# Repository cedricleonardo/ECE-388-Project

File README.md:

# ECE-388-Project

DC Programmable Load project for ECE 388

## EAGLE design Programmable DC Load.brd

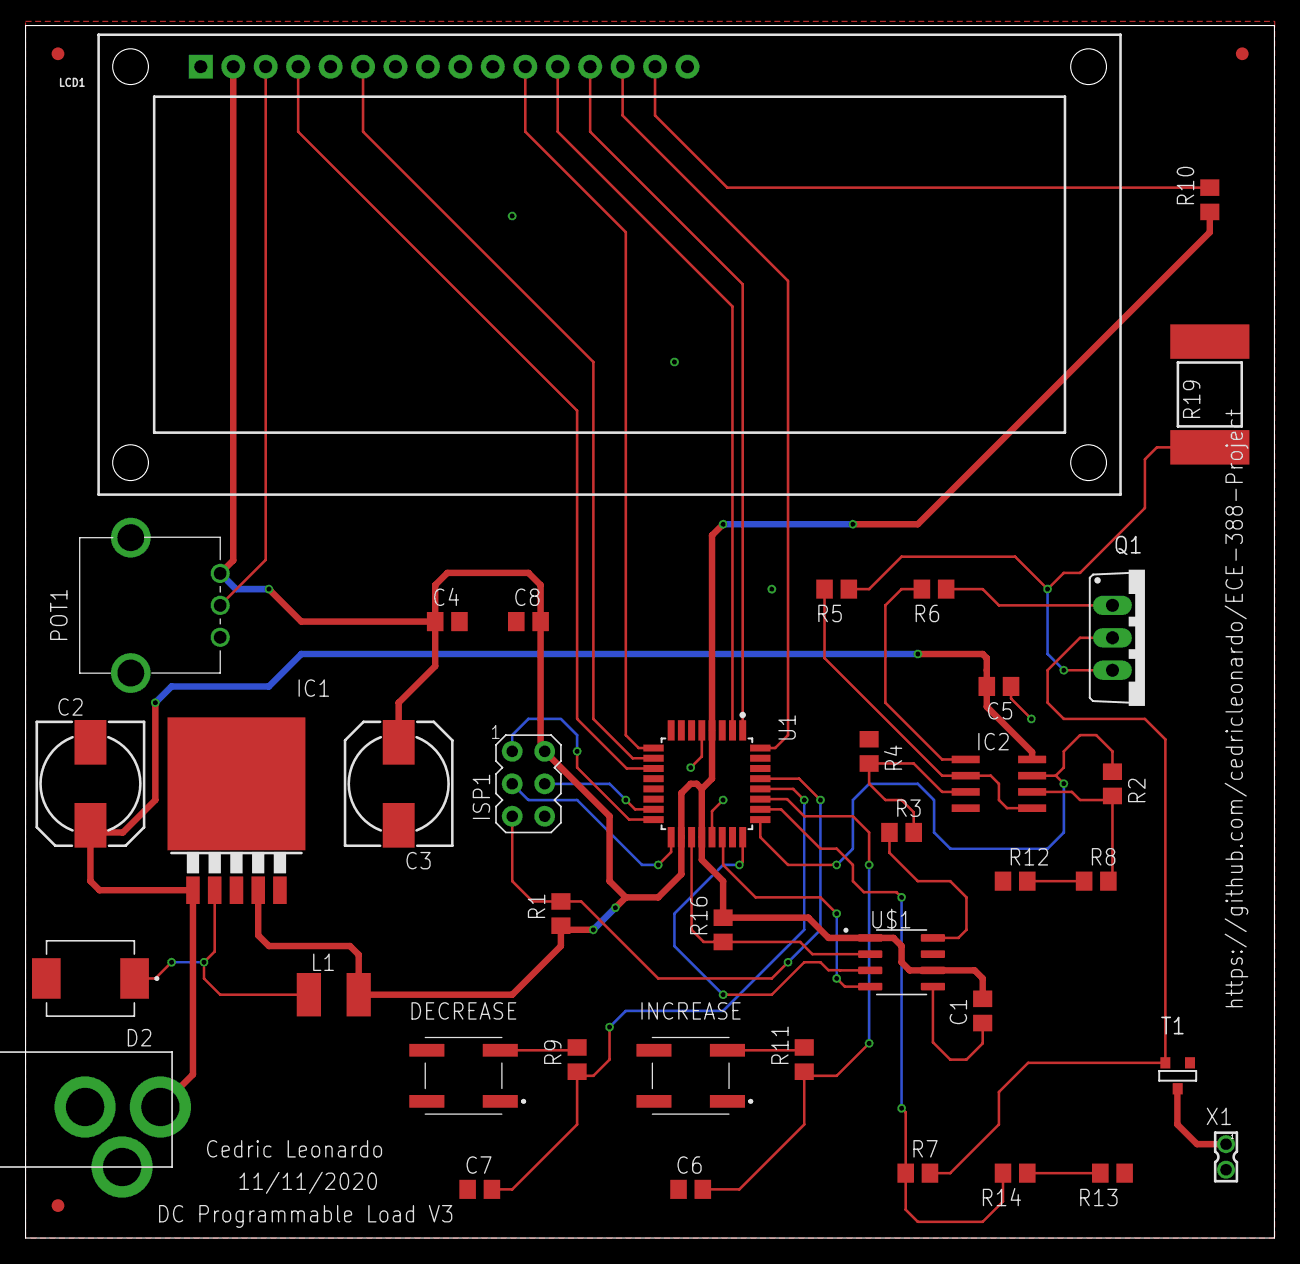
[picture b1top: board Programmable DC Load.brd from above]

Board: 2 copper layers, 97.8 x 94.9 mm, 42 parts (0 on the bottom side), 37 nets.

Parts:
C1, C5, C8: 0.1 uF; C0805
C2: 680 uF; 140CLH-0810
C3: 220 uF; 140CLH-0810
C4, C6, C7: 100 nF; C0805
D2: SS34; DIOM7959X265N
DECREASE: EVP-BFAC1A000; EVPBFAC1A000
IC1: LM2596S; TO263-5
IC2: LM358MX; SO08
INCREASE: EVP-BFAC1A000; EVPBFAC1A000
ISP1: AVRISP-6; AVRISP
L1: 33 uH; L1812
LCD1: LCD-16X2SILK; LCD-16X2
POT1: RK09K1130A5R
Q1: IRF540; TO220BV
R1, R2, R3, R4, R5, R6, R7, R16: 10k; R0805
R8, R9, R11, R12, R13, R14: 1k; R0805
R10: 560; R0805
R19: 0.1R5W; BVS
T1: SOT-23
U1: ATMEGA328PB-AU; QFP80P900X900X120-32N
U$1: MCP4921-E/SN; SOIC127P600X175-8N
U$2, U$3, U$4: FIDUCIAL; FIDUCIAL_1MM
U$6: 2.1MMJACKTHM; PJ-102A
X1: 332-02

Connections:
+5V: C1.2, C3.+, C4.1, C8.2, IC1.4, ISP1.2, L1.2, LCD1.2, POT1.VCC, R1.1, R10.1, R16.2, U1.4, U1.18, U1.20, U$1.1, U$1.6
+12V: C2.+, C5.2, IC1.1, IC2.8, U$6.TIP
CS: R16.1, U1.19, U$1.2
CURRENT_SENSE: IC2.7, R2.1, U1.25
GND: C2.-, C3.-, C4.2, C5.1, C6.1, C7.1, C8.1, D2.A, DECREASE.A1, IC1.3, IC1.5, IC1.6, IC2.4, INCREASE.A1, ISP1.6, LCD1.1, LCD1.5, LCD1.16, POT1.GND, R4.1, R12.1, R13.1, R19.2, T1.3, U1.5, U1.21, U$1.7, U$6.RING, U$6.RING_SW, X1.2
unnamed: R8.1, R12.2
unnamed: R13.2, R14.1
unnamed: LCD1.15, R10.2
unnamed: D2.C, IC1.2, L1.1
unnamed: T1.1, X1.1
unnamed: DECREASE.B1, R9.2
unnamed: INCREASE.B1, R11.2
unnamed: IC2.3, R3.2, R4.2
unnamed: LCD1.3, POT1.OUT
unnamed: IC2.1, R6.2
unnamed: Q1.G, R6.1
unnamed: IC2.2, IC2.5, R5.2
unnamed: Q1.S, R5.1, R19.1
unnamed: Q1.D, R7.2, T1.2
unnamed: IC2.6, R2.2, R8.2
unnamed: R3.1, U$1.8
unnamed: C1.1, U$1.5
PB3: ISP1.4, U1.15
PB4: ISP1.1, U1.16
PB5: ISP1.3, U1.17
PC4: C6.2, R11.1, U1.27
PC5: C7.2, R9.1, U1.28
PD2: LCD1.14, U1.32
PD3: LCD1.13, U1.1
PD4: LCD1.12, U1.2
PD5: LCD1.11, U1.9
PD6: LCD1.6, U1.10
PD7: LCD1.4, U1.11
RESET: ISP1.5, R1.2, U1.29
SCK: U1.24, U$1.3
SDI: U1.22, U$1.4
VOLTAGE_SENSE: R7.1, R14.2, U1.26

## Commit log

2020-11-06 Rename renders/Gerber/Programmable DC Load.GBL to renders/Gerb/Programmable DC Load.GBL
2020-11-06 Rename renders/Gerber/Programmable DC Load.GBO to renders/Gerb/Programmable DC Load.GBO
2020-11-06 Rename renders/Gerber/Programmable DC Load.GBP to renders/Gerb/Programmable DC Load.GBP
2020-11-06 Rename renders/Gerber/Programmable DC Load.GBS to renders/Gerb/Programmable DC Load.GBS
2020-11-06 Rename renders/Gerber/Programmable DC Load.GKO to renders/Gerb/Programmable DC Load.GKO
2020-11-06 Rename renders/Gerber/Programmable DC Load.GTL to renders/Gerb/Programmable DC Load.GTL
2020-11-06 Rename renders/Gerber/Programmable DC Load.GTO to renders/Gerb/Programmable DC Load.GTO
2020-11-06 Rename renders/Gerber/Programmable DC Load.GTP to renders/Gerb/Programmable DC Load.GTP
2020-11-06 Rename renders/Gerber/Programmable DC Load.GTS to renders/Gerb/Programmable DC Load.GTS
2020-11-06 Rename renders/Gerber/Programmable DC Load.TXT to renders/Gerb/Programmable DC Load.TXT
2020-11-06 Rename renders/Gerber/gerber_job.gbrjob to renders/Gerb/gerber_job.gbrjob
2020-11-07 Create cam
2020-11-07 Rename cam to empty.txt
2020-11-11 Create CAMOutputs

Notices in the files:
parts and their libraries:
SparkFun-Displays: Licensing: Creative Commons ShareAlike 4.0 International - https://creativecommons.org/licenses/by-sa/4.0
